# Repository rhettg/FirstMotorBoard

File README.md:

# First Motor Driver Board

My first PCB design.

Trying to drive four motors off a Freenove ESP32-S3 WROOM dev board.

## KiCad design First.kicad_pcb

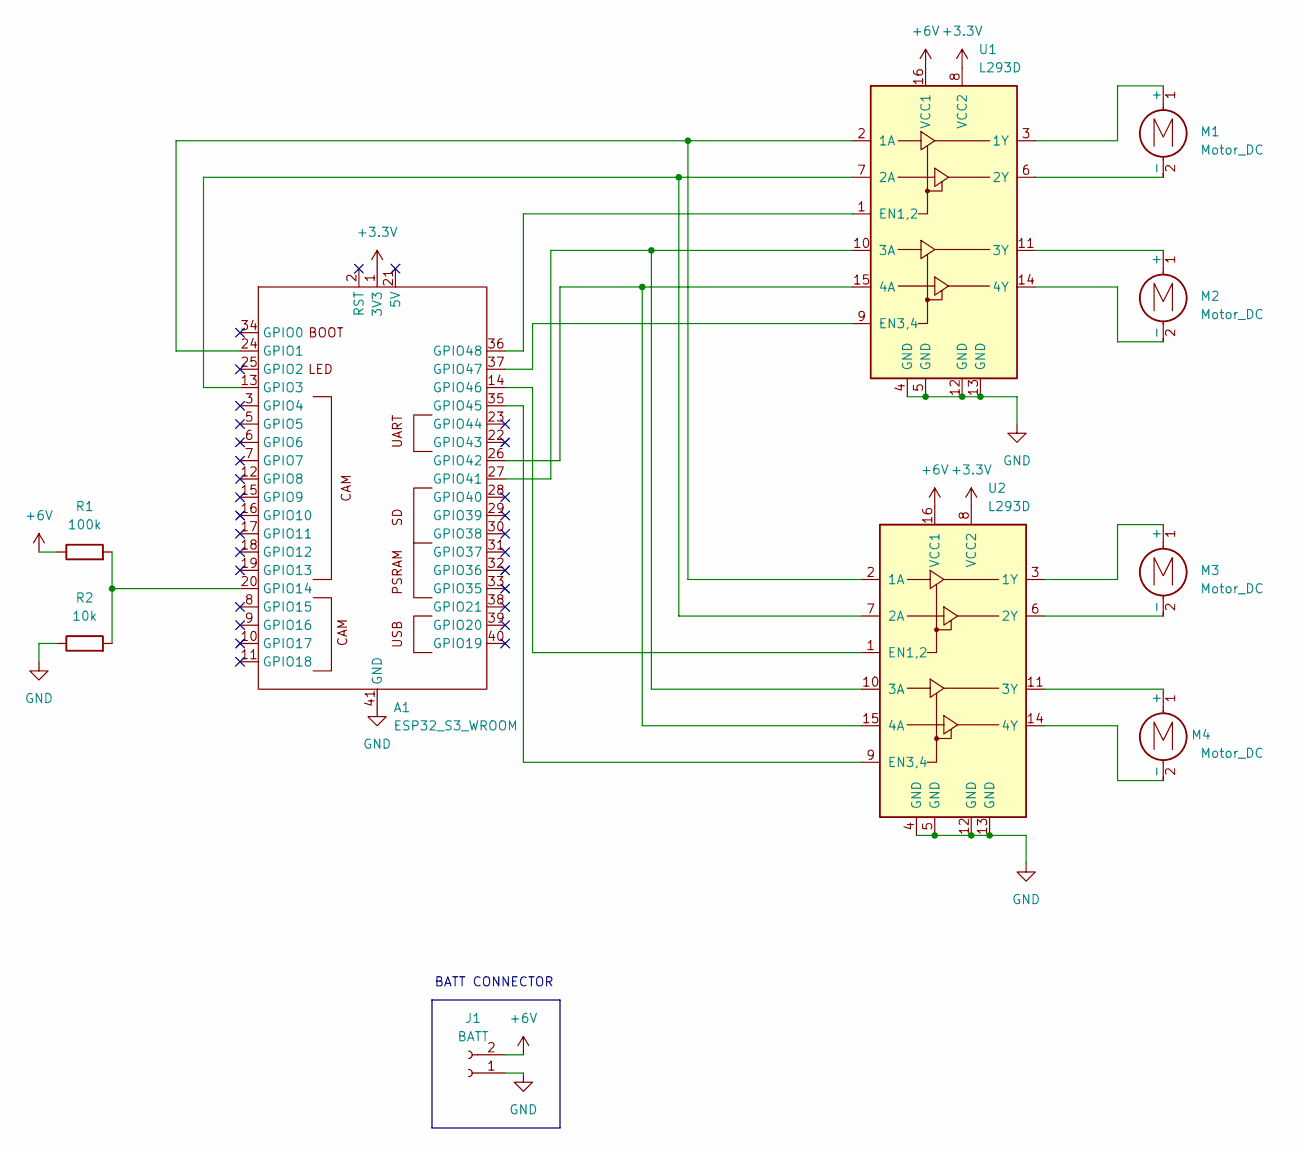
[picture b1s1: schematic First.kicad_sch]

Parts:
A1: ESP32_S3_WROOM; FREENOVE ESP32-S3 WROOM
J1: BATT; PinHeader_1x02_P2.54mm_Vertical
M1, M2, M3, M4: Motor_DC; JST_XH_B2B-XH-A_1x02_P2.50mm_Vertical
R1: 100k; R_Axial_DIN0207_L6.3mm_D2.5mm_P10.16mm_Horizontal
R2: 10k; R_Axial_DIN0207_L6.3mm_D2.5mm_P10.16mm_Horizontal
U1, U2: L293D; DIP-16_W7.62mm

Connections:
+3.3V: A1.1 (3V3), U1.8 (VCC2), U2.8 (VCC2)
+6V: J1.2, R1.1, U1.16 (VCC1), U2.16 (VCC1)
GND: A1.41 (GND), J1.1, R2.1, U1.4 (GND), U1.5 (GND), U1.12 (GND), U1.13 (GND), U2.4 (GND), U2.5 (GND), U2.12 (GND), U2.13 (GND)
unnamed: A1.24 (GPIO1), U1.2 (1A), U2.2 (1A)
unnamed: A1.13 (GPIO3), U1.7 (2A), U2.7 (2A)
unnamed: A1.20 (GPIO14), R1.2, R2.2
unnamed: A1.27 (GPIO41), U1.10 (3A), U2.10 (3A)
unnamed: A1.26 (GPIO42), U1.15 (4A), U2.15 (4A)
unnamed: A1.35 (GPIO45), U2.9 (EN3,4)
unnamed: A1.14 (GPIO46), U2.1 (EN1,2)
unnamed: A1.37 (GPIO47), U1.9 (EN3,4)
unnamed: A1.36 (GPIO48), U1.1 (EN1,2)
unnamed: M1.1 (+), U1.3 (1Y)
unnamed: M1.2 (-), U1.6 (2Y)
unnamed: M2.1 (+), U1.11 (3Y)
unnamed: M2.2 (-), U1.14 (4Y)
unnamed: M3.1 (+), U2.3 (1Y)
unnamed: M3.2 (-), U2.6 (2Y)
unnamed: M4.1 (+), U2.11 (3Y)
unnamed: M4.2 (-), U2.14 (4Y)

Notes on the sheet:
BATT CONNECTOR

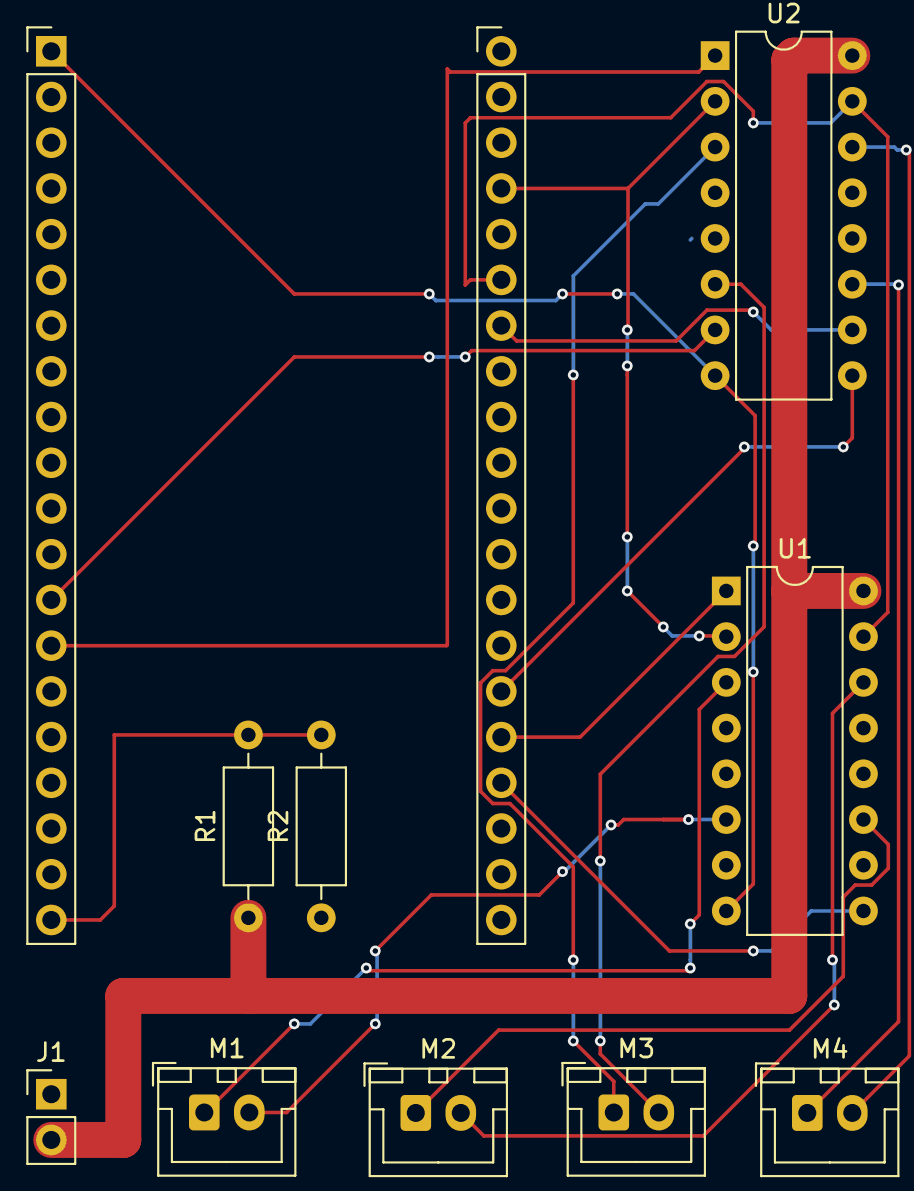
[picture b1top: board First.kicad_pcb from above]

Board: 2 copper layers, 10 parts (0 on the bottom side), 20 nets.

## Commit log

2024-04-05 initial checkin
